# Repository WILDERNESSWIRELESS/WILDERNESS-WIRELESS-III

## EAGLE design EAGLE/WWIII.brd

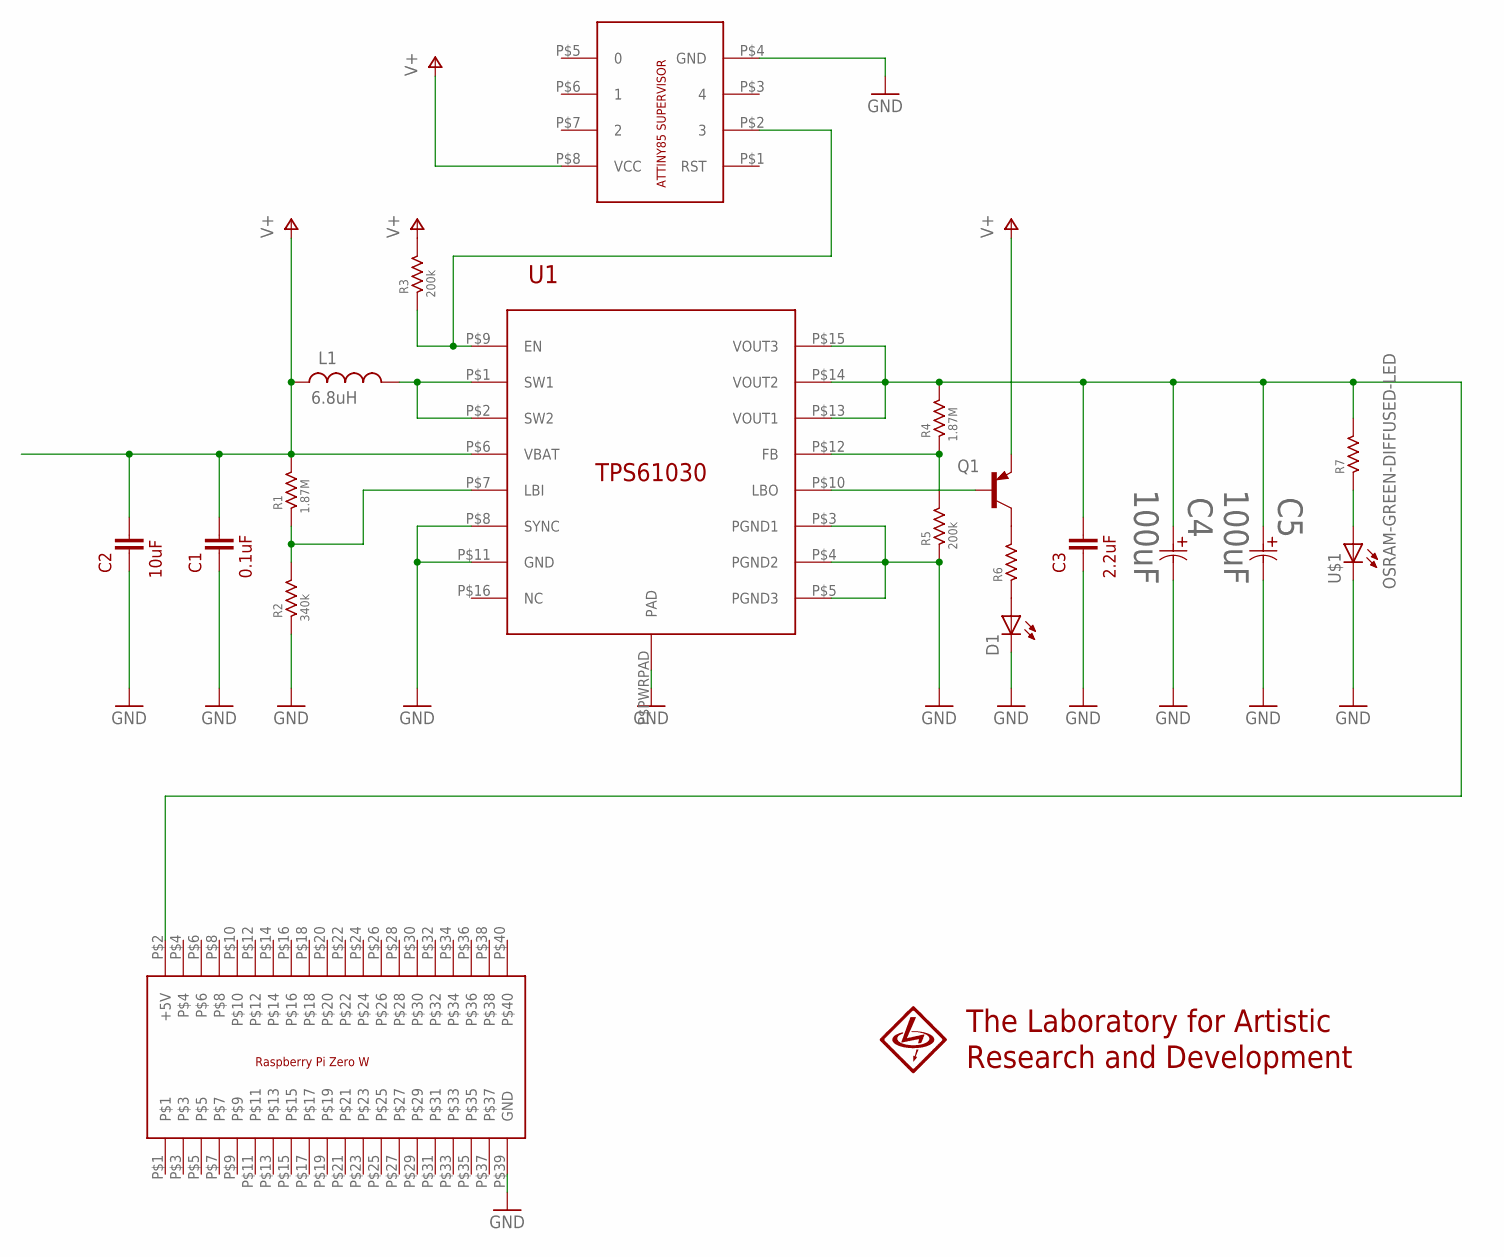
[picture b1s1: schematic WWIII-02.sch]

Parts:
C1: 0.1uF; 0805
C2: 10uF; KEM_C1006_X5R_SMD
C3: 2.2uF; CAP-X5R
C4, C5: 100uF; CAP_EEE_C
D1: OSRAM-RED-DIFFUSED-LED; OSRAM_CHIPLED
L1: 6.8uH; MLZ2012
Q1: ON-SEMI-SMD-PREBIAS-TRANS-SOT23; SOT23-3
R1: 1.87M; RC0805N
R2: 340k; RC0805N
R3, R5: 200k; RESISTOR-0805
R4: 1.87M; PANASONIC-SMD-RESISTOR-0805
R6, R7: YAGEO-SMD-1/8W-RESISTOR-0805; RC0805N
U1: TPS61030; TPS61030PWPR
U2: RASPBERRY-PI
U3: ATTINY-SUPERVISOR; ATTINY-SOCKETED
U$1: OSRAM-GREEN-DIFFUSED-LED; OSRAM_CHIPLED

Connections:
GND: C1.1, C2.1, C3.1, C4.2 (22), C5.2 (22), D1.P$2 (2), R2.1, R5.1, U1.P$3 (PGND1), U1.P$4 (PGND2), U1.P$5 (PGND3), U1.P$8 (SYNC), U1.P$11 (GND), U1.P$PWRPAD (PAD), U2.P$39 (GND), U3.P$4 (GND), U$1.P$2 (2)
unnamed: R4.P$1, R5.2, U1.P$12 (FB)
unnamed: L1.2, U1.P$1 (SW1), U1.P$2 (SW2)
unnamed: C3.2, C4.1 (11), C5.1 (11), R4.P$2, R7.2, U1.P$13 (VOUT1), U1.P$14 (VOUT2), U1.P$15 (VOUT3), U2.P$2 (+5V)
unnamed: R7.1, U$1.P$1 (1)
unnamed: R1.1, R2.2, U1.P$7 (LBI)
unnamed: Q1.1, U1.P$10 (LBO)
unnamed: R3.1, U1.P$9 (EN), U3.P$2 (3)
unnamed: Q1.3, R6.2
unnamed: D1.P$1 (1), R6.1
V+: C1.2, C2.2, L1.1, Q1.2, R1.2, R3.2, U1.P$6 (VBAT), U3.P$8 (VCC)

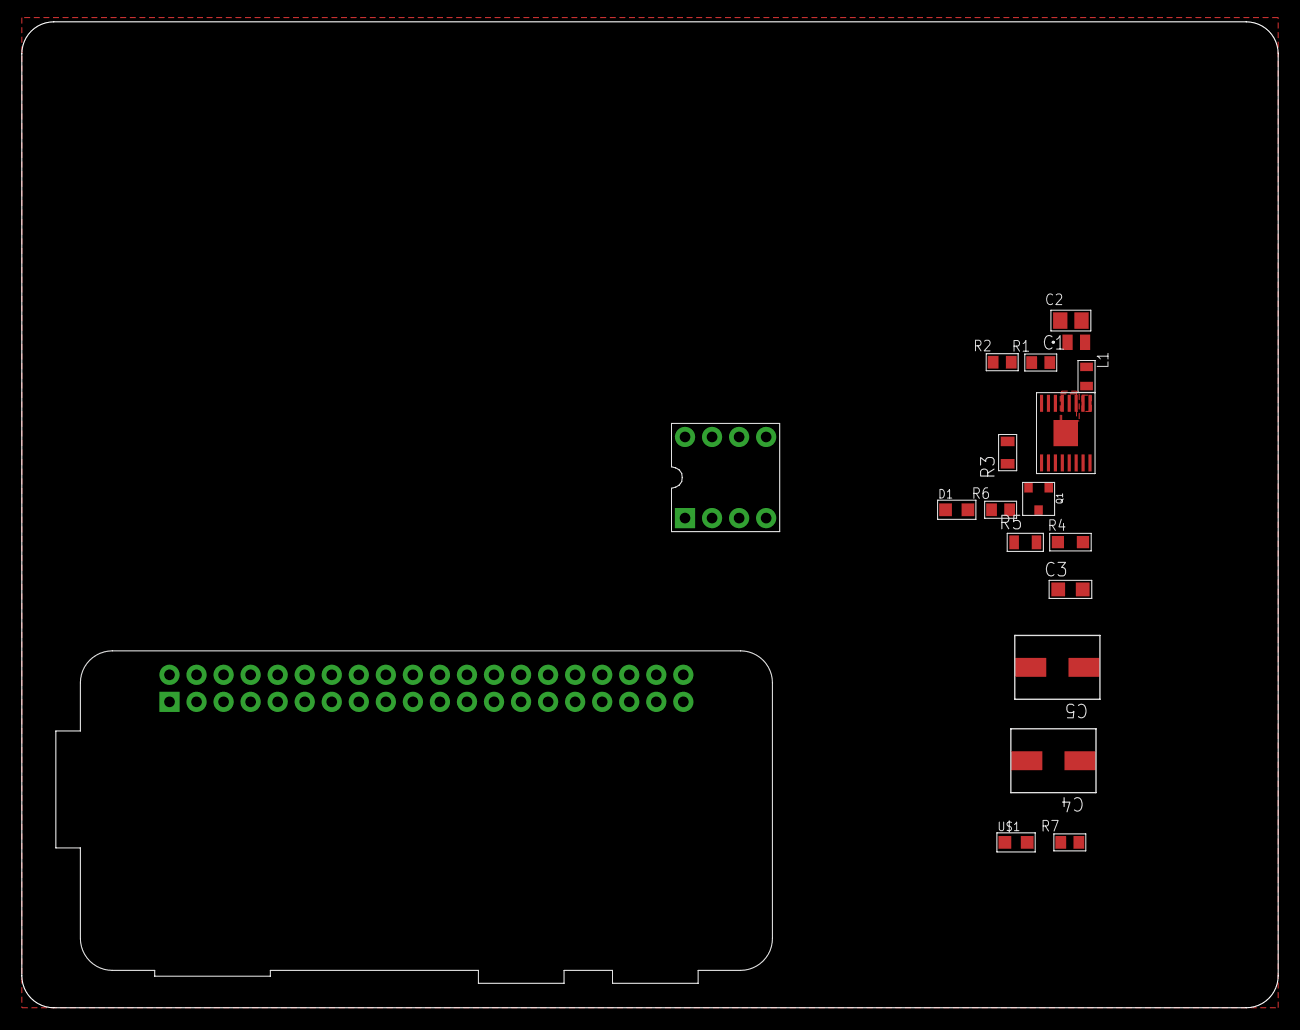
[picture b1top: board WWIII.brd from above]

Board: 2 copper layers, 118.0 x 92.6 mm, 19 parts (0 on the bottom side), 11 nets.

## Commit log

2018-06-24 cleaning up
2018-07-02 tweaks
2018-07-15 readings
2018-07-27 adding drivers
2018-08-02 adding rules
2018-08-05 added arduino firmware
2018-08-27 fritzing pdf
